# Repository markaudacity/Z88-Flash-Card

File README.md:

# Z88 Flash/RAM Card

&emsp;<br />
An open-source expansion card for the Cambridge Z88 which can be configured as 512KB RAM, 1MB RAM or 1MB Flash. 
This is an updated version using a currently-available (as of early 2025) flash chip, as neither the original part used (an AM29F080) nor a pin-compatible part are available new. Originally created by Jim Conner, with groundwork by XavSnap. Please see upstream for notes on the original design.

This work is based upon the Z88 connector design shared by XavSnap at [SinclairZXWorld Z88 Forum](https://sinclairzxworld.com/viewtopic.php?f=24&t=4431) - Thank you XavSnap!

# Current Status
This commit is the untested, modified version of the v3.0 card. It should work as-is, as the circuit is unchanged with the exception of the pinout of the new part, but I have not etched a board or built a prototype yet, so this should be considered alpha hardware that may break your Z88, sleep with your wife, burn down your house, and all kinds of mean, ugly, nasty things besides.

# What's Been Done

- schematic updated for currently-available TSOP-48 8Mbit flash chip
- PCB layout reworked for same, including cleaning up trace routing, reducing the number of vias, and general neatening and tidying
- symbol and footprint added for JEDEC-standard AM29F800-compatible part in TSOP-48 I package
- URL and maker names updated to point to this repository

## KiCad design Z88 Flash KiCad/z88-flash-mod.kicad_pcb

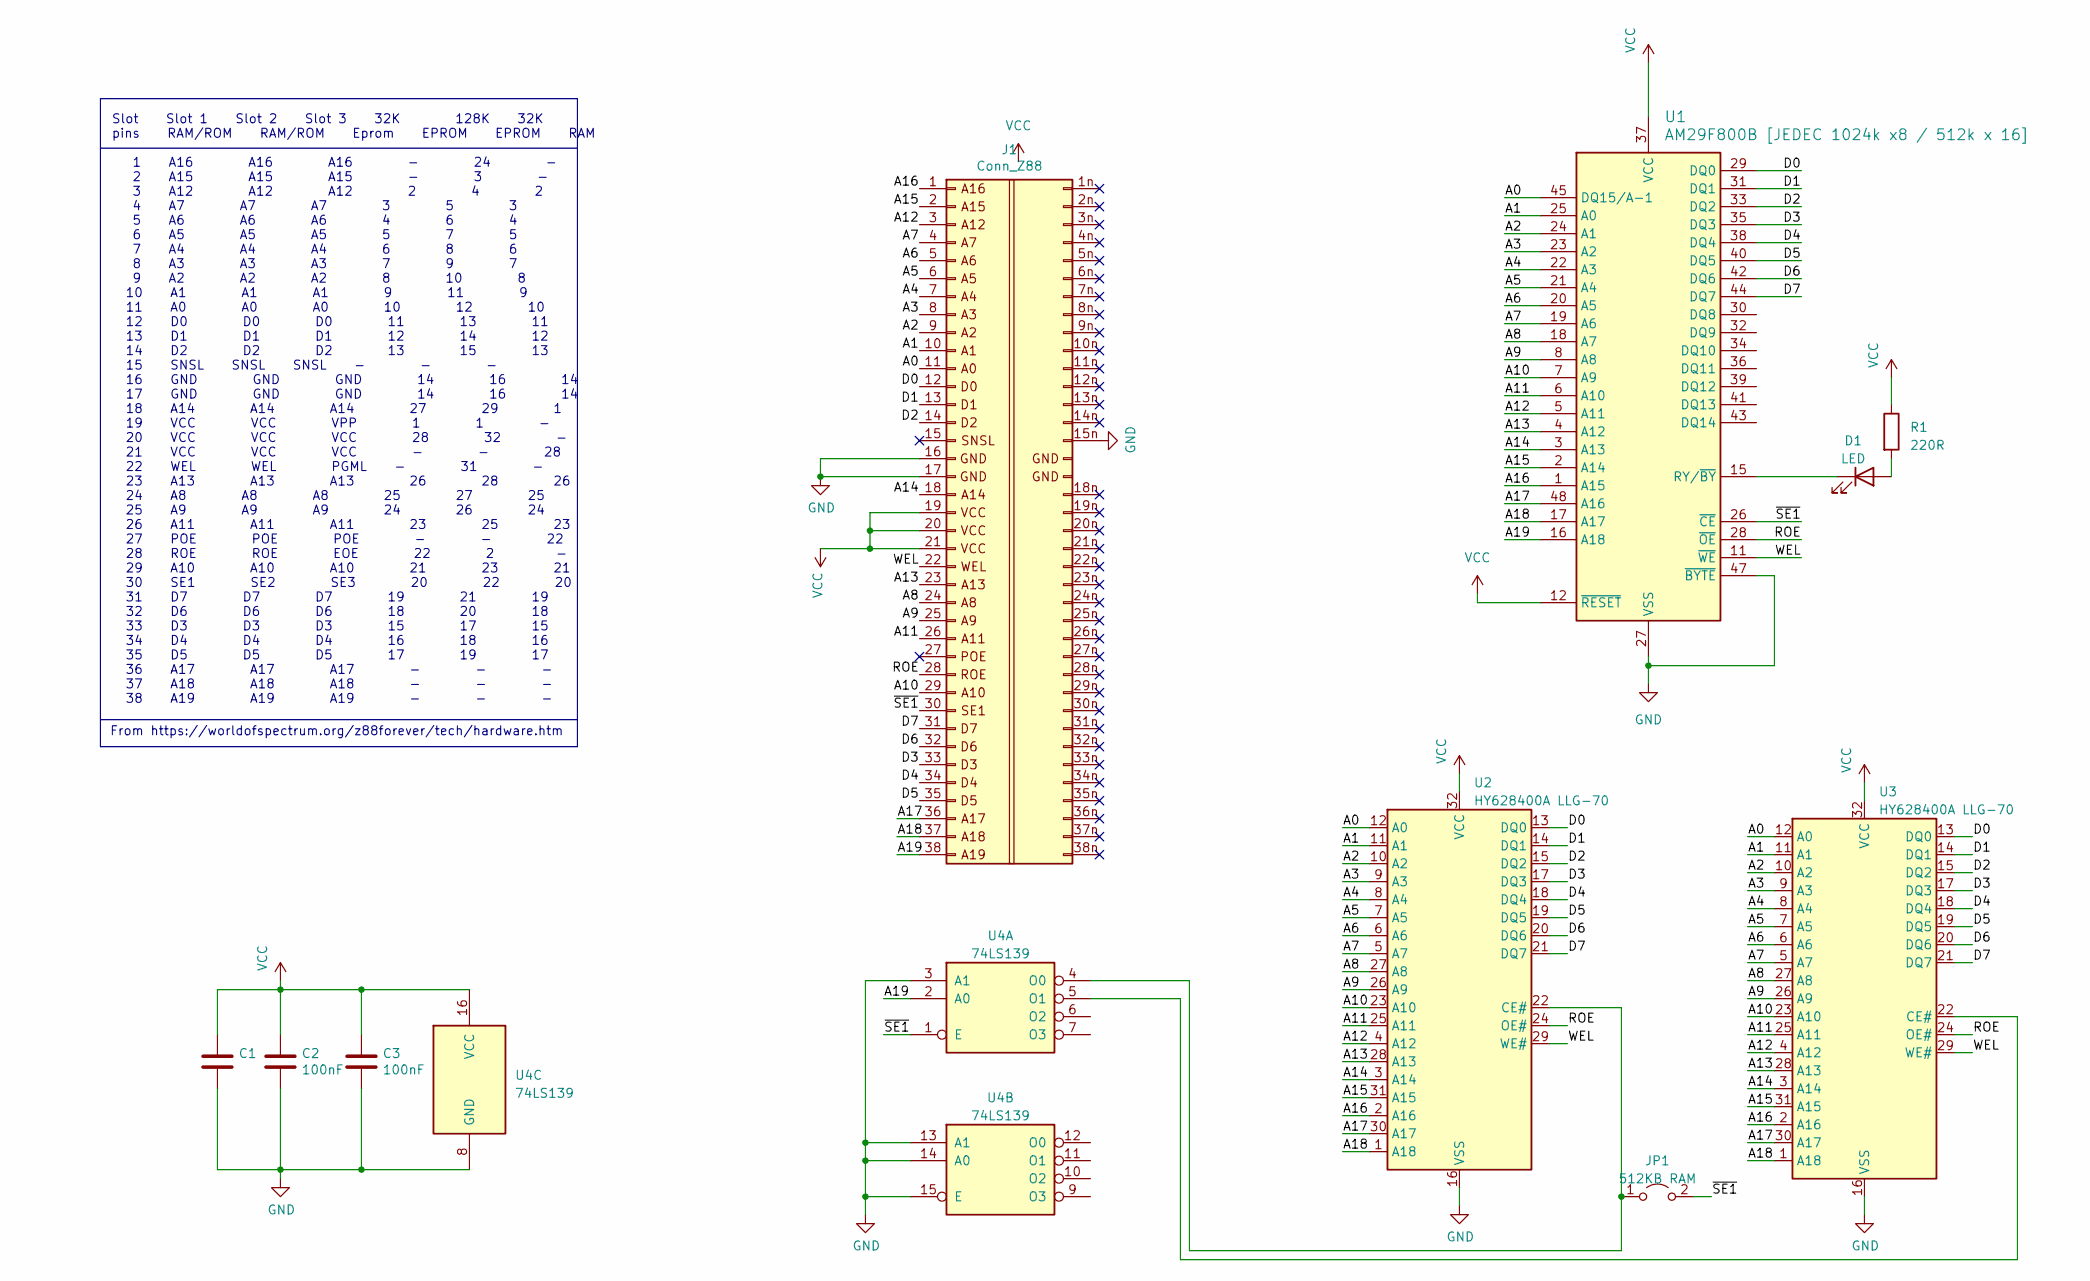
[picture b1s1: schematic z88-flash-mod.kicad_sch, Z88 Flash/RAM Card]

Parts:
C1, C2, C3: 100nF; C_1206_3216Metric
D1: LED; LED_1206_3216Metric
J1: Conn_Z88; Z88_connector
JP1: 512KB RAM; SolderJumper-2_P1.3mm_Open_Pad1.0x1.5mm
R1: 220R; R_0805_2012Metric_Pad1.20x1.40mm_HandSolder
U1: AM29F800B [JEDEC 1024k x8 / 512k x 16]; TSOP-I-48_18.4x12mm_P0.5mm
U2, U3: HY628400A LLG-70; SSOP-32_11.305x20.495mm_P1.27mm
U4: 74LS139; SO-16_3.9x9.9mm_P1.27mm

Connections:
/A0: J1.11, U1.45 (DQ15/A-1), U2.12 (A0), U3.12 (A0)
/A1: J1.10, U1.25 (A0), U2.11 (A1), U3.11 (A1)
/A2: J1.9, U1.24 (A1), U2.10 (A2), U3.10 (A2)
/A3: J1.8, U1.23 (A2), U2.9 (A3), U3.9 (A3)
/A4: J1.7, U1.22 (A3), U2.8 (A4), U3.8 (A4)
/A5: J1.6, U1.21 (A4), U2.7 (A5), U3.7 (A5)
/A6: J1.5, U1.20 (A5), U2.6 (A6), U3.6 (A6)
/A7: J1.4, U1.19 (A6), U2.5 (A7), U3.5 (A7)
/A8: J1.24, U1.18 (A7), U2.27 (A8), U3.27 (A8)
/A9: J1.25, U1.8 (A8), U2.26 (A9), U3.26 (A9)
/A10: J1.29, U1.7 (A9), U2.23 (A10), U3.23 (A10)
/A11: J1.26, U1.6 (A10), U2.25 (A11), U3.25 (A11)
/A12: J1.3, U1.5 (A11), U2.4 (A12), U3.4 (A12)
/A13: J1.23, U1.4 (A12), U2.28 (A13), U3.28 (A13)
/A14: J1.18, U1.3 (A13), U2.3 (A14), U3.3 (A14)
/A15: J1.2, U1.2 (A14), U2.31 (A15), U3.31 (A15)
/A16: J1.1, U1.1 (A15), U2.2 (A16), U3.2 (A16)
/A17: J1.36, U1.48 (A16), U2.30 (A17), U3.30 (A17)
/A18: J1.37, U1.17 (A17), U2.1 (A18), U3.1 (A18)
/A19: J1.38, U1.16 (A18), U4.2 (A0)
/D0: J1.12, U1.29 (DQ0), U2.13 (DQ0), U3.13 (DQ0)
/D1: J1.13, U1.31 (DQ1), U2.14 (DQ1), U3.14 (DQ1)
/D2: J1.14, U1.33 (DQ2), U2.15 (DQ2), U3.15 (DQ2)
/D3: J1.33, U1.35 (DQ3), U2.17 (DQ3), U3.17 (DQ3)
/D4: J1.34, U1.38 (DQ4), U2.18 (DQ4), U3.18 (DQ4)
/D5: J1.35, U1.40 (DQ5), U2.19 (DQ5), U3.19 (DQ5)
/D6: J1.32, U1.42 (DQ6), U2.20 (DQ6), U3.20 (DQ6)
/D7: J1.31, U1.44 (DQ7), U2.21 (DQ7), U3.21 (DQ7)
/ROE: J1.28, U1.28 (~OE), U2.24 (OE#), U3.24 (OE#)
/WEL: J1.22, U1.11 (~WE), U2.29 (WE#), U3.29 (WE#)
/~SE1: J1.30, JP1.2 (B), U1.26 (~CE), U4.1 (E)
GND: C1.2, C2.2, C3.2, J1.15n (Pin_53), J1.16 (GND), J1.17 (GND), U1.27 (VSS), U1.46 (VSS), U1.47 (~BYTE), U2.16 (VSS), U3.16 (VSS), U4.3 (A1), U4.8 (GND), U4.13 (A1), U4.14 (A0), U4.15 (E)
unnamed: D1.2 (A), R1.2
unnamed: D1.1 (K), U1.15 (RY/~BY)
unnamed: JP1.1 (A), U2.22 (CE#), U4.4 (O0)
unnamed: U3.22 (CE#), U4.5 (O1)
VCC: C1.1, C2.1, C3.1, J1.19, J1.20, J1.21, R1.1, U1.12 (~RESET), U1.37 (VCC), U2.32 (VCC), U3.32 (VCC), U4.16 (VCC)

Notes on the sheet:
From https://worldofspectrum.org/z88forever/tech/hardware.htm
Slot Slot 1 Slot 2 Slot 3 32K 128K 32K pins RAM/ROM RAM/ROM Eprom EPROM EPROM RAM 1 A16 A16 A16 - 24 - 2 A15 A15 A15 - 3 - 3 A12 A12 A12 2 4 2 4 A7 A7 A7 3 5 3 5 A6 A6 A6 4 6 4 6 A5 A5 A5 5 7 5 7 A4 A4 A4 6 8 6 8 A3 A3 A3 7 9 7 9 A2 A2 A2 8 10 8 10 A1 A1 A1 9 11 9 11 A0 A0 A0 10 12 10 12 D0 D0 D0 1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

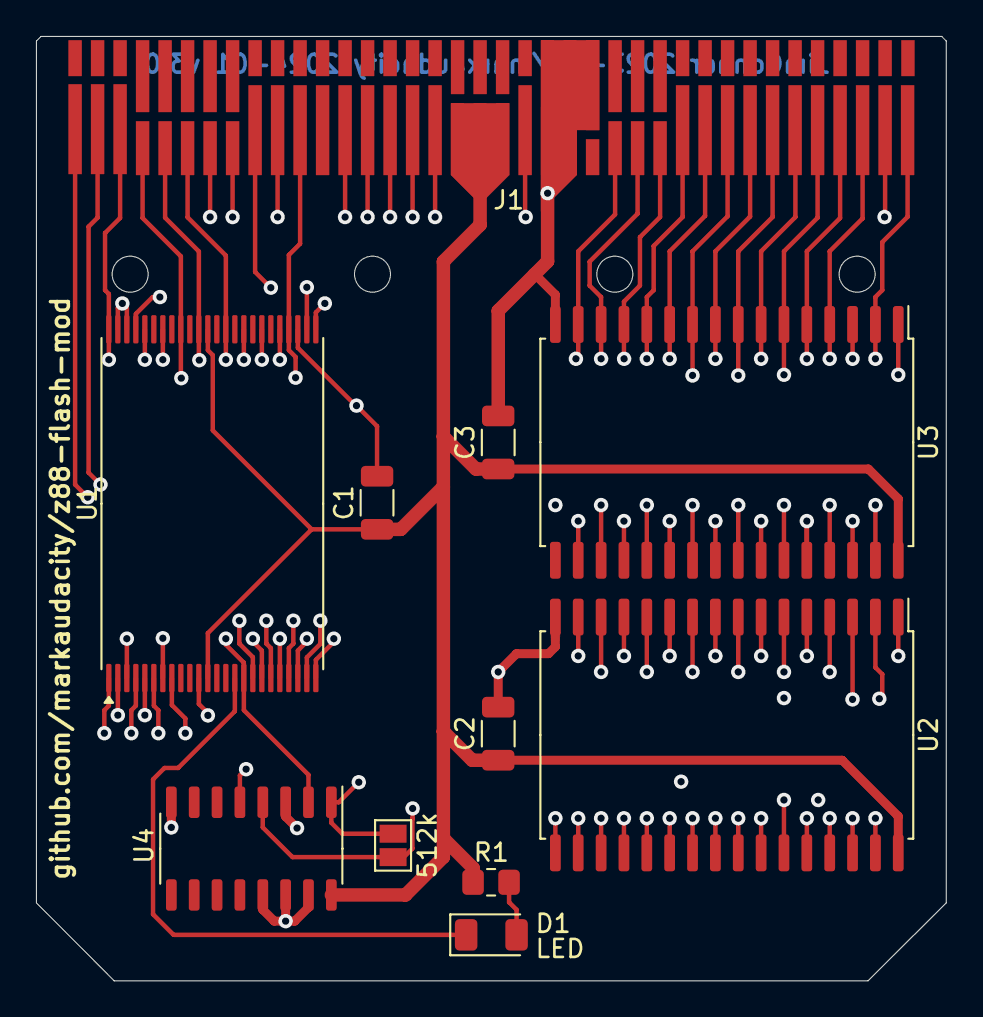
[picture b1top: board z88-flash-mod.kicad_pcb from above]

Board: 4 copper layers, 50.5 x 52.5 mm, 12 parts (1 on the bottom side), 37 nets.

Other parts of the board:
QR_code: LOGO

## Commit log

2025-01-02 initial upload of modified files, removal of upstream files
2025-01-02 removed connector-backups dir
2025-01-02 new Gerbers
2025-01-02 ZIPped up neew Gerbers for easy fab upload
2025-01-02 new board routing and render images
2025-01-02 On branch main Your branch is up to date with 'origin/main'.
    Changes to be committed:
    new file: PCB-3D-render 2025.png
    new file: PCB-Routing 2025.png
    new file: Z88_1MB_Flash/Z88-1MB-Flash-mod.zip
    new file: Z88_1MB_Flash/z88-flash-mod-backups/z88-flash-mod-2025-01-02_165429.zip
2025-01-02 added images to README.md
2025-01-02 actually changing the images dir lol
2025-01-02 Changes to be committed: modified: README.md deleted: images/PCB-3D-render 2025.png deleted: images/PCB-Routing 2025.png
    Untracked files:
    images/PCB-3D-render-2025.png
    images/PCB-Routing-2025.png
2025-01-02 Changes to be committed: new file: images/PCB-3D-render-2025.png new file: images/PCB-Routing-2025.png
2025-01-02 trying to get images to render at size
2025-01-02 Revert "trying to get images to render at size"
    This reverts commit 511093792c906d30c7fcdc7c80e52c18435d85d8.
    Changes to be committed:
    modified: README.md
2025-01-02 Changes to be committed: modified: README.md
2025-01-06 minor edits
2025-01-06 rename images
2025-01-07 organize
2025-01-08 corrected Jim's surname. Sorry Jim!
2025-01-13 small tweaks to schematic, silkscreen, edge cuts, added PDF plot of schematic
2025-01-14 file cleanup
